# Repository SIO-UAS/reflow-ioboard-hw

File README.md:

# reflow-ioboard-hw
A general purpouse microcontroller board with electronics to read a pt1000 up to 300°C

# why this was designed
This board was designed to modify a genric small oven to reflow solder in it. 
The whole idea behind it was to make a very fancy reflow oven, where the UI and controlling is managed by a RPI with a touchscreen.
To Interface with a RPI there is a I2C Port on the side (the PI should also power the board via 3,3V. Yet the relays should be powerd via a 5V powersupply).
It feauters 3 screwterminals dedicated to drive relays (mosfet, no driver), 2 leds and some IO Ports.

I used a Heraeus Nexensos W-EYK 6 PT1000 aus PT1000. (Conrad Art Nr: 000172430)
Eventually you have to recalulate the resitors for the amplifier.

Yet you can use this board for many different applications.

# wireing

I hope the labeles on the board are clear enough

# software
A first version has been made. To bee seen in an other repository. 

# assembling
To assemble this board reflow soldering is adviced. (How Ironic)
I used maker paste, a stencil and a pan and some screws.

I hope this project helps you.
You are free to use it.
You are free to modify it.

Please Note: This is a project I done private, so don't expect it to be beuatiful :P

Sorry for my bad english, I'm hungry :P

If you want to support my Projects: Here is a link to Aisler where you can order the PCB (Warning: Diodes and Mosfet are not assigned):
https://aisler.net/p/IZKNMKIW

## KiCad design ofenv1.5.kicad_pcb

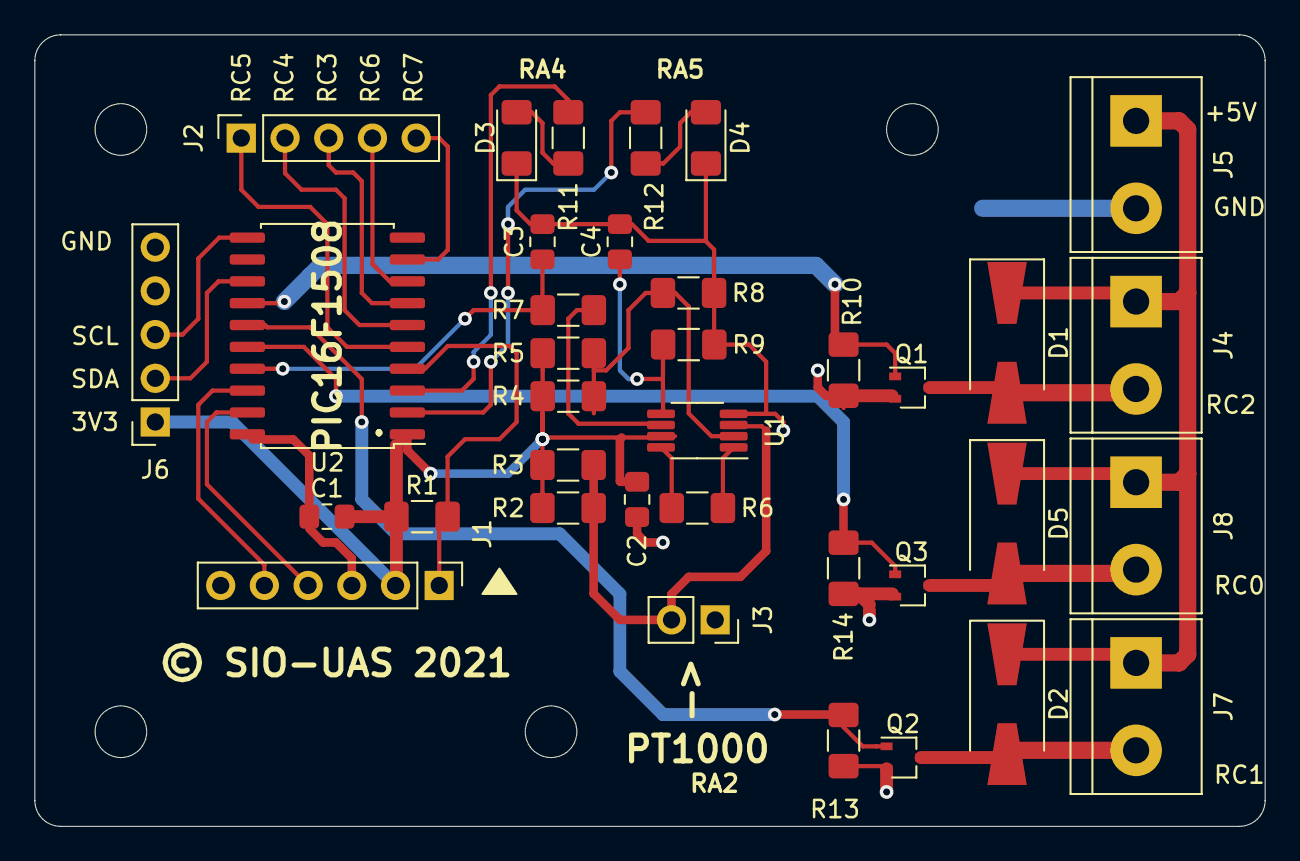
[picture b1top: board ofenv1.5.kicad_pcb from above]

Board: 2 copper layers, 71.5 x 46.0 mm, 40 parts (0 on the bottom side), 30 nets.

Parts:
C1, C2: 0.1u; C_0805_2012Metric_Pad1.15x1.40mm_HandSolder
C3: 1u; C_0805_2012Metric_Pad1.15x1.40mm_HandSolder
C4: 1n; C_0805_2012Metric_Pad1.15x1.40mm_HandSolder
D1, D2, D5: D_Schottky; D_SMA-SMB_Universal_Handsoldering
D3, D4: LED; LED_1206_3216Metric_Pad1.42x1.75mm_HandSolder
H1, H2, H3, H4: MountingHole; MountingHole_3mm
J1: Conn_PIC_ICSP_ICD; PinHeader_1x06_P2.54mm_Vertical
J2, J6: Conn_01x05_Female; PinSocket_1x05_P2.54mm_Vertical
J3: Conn_01x02; PinSocket_1x02_P2.54mm_Vertical
J4, J5, J7, J8: Screw_Terminal_01x02; TerminalBlock_bornier-2_P5.08mm
Q1, Q2, Q3: BSS214NW; SOT-323_SC-70
R1, R6: 4k7; R_1206_3216Metric_Pad1.42x1.75mm_HandSolder
R2, R3, R4, R5, R9: 100k; R_1206_3216Metric_Pad1.42x1.75mm_HandSolder
R7: 100; R_1206_3216Metric_Pad1.42x1.75mm_HandSolder
R8, R10, R13, R14: 1k; R_1206_3216Metric_Pad1.42x1.75mm_HandSolder
R11, R12: 120; R_1206_3216Metric_Pad1.42x1.75mm_HandSolder
U1: INA326; MSOP-8_3x3mm_P0.65mm
U2: PIC16F1508-ISO; SOIC-20W_7.5x12.8mm_P1.27mm

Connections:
+3V3: C1.2, C2.2, J1.2, J6.1, R1.1, R2.1, R3.1, R4.1, R5.1, U1.7, U2.1
+VSW: D1.1, D2.1, D5.1, J4.1, J5.1, J7.1, J8.1
GND: C1.1, C2.1, C3.2, C4.2, D3.1, D4.1, J1.3, J3.1, J5.2, J6.5, Q1.2, Q2.2, Q3.2, R8.2, R9.2, R10.2, R13.2, R14.2, U1.4, U2.20
unnamed: C3.1, R7.1, U2.17
unnamed: C4.1, R9.1, U1.5
unnamed: D1.2, J4.2, Q1.3
unnamed: D2.2, J7.2, Q2.3
unnamed: D3.2, R11.2
unnamed: D4.2, R12.2
unnamed: D5.2, J8.2, Q3.3
unnamed: J1.1, R1.2, U2.4
unnamed: J1.4, U2.19
unnamed: J1.5, U2.18
unnamed: J2.1, U2.5
unnamed: J2.2, U2.6
unnamed: J2.3, U2.7
unnamed: J2.4, U2.8
unnamed: J2.5, U2.9
unnamed: J3.2, R2.2, R3.2, U1.3
unnamed: J6.2, U2.13
unnamed: J6.3, U2.11
unnamed: Q1.1, R10.1, U2.14
unnamed: Q2.1, R13.1, U2.15
unnamed: Q3.1, R14.1, U2.16
unnamed: R4.2, R5.2, R8.1, U1.2
unnamed: R6.1, U1.1
unnamed: R6.2, U1.8
unnamed: R7.2, U1.6
unnamed: R11.1, U2.3
unnamed: R12.1, U2.2

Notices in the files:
ofenv1.5.kicad_pcb:
© SIO-UAS 2021
